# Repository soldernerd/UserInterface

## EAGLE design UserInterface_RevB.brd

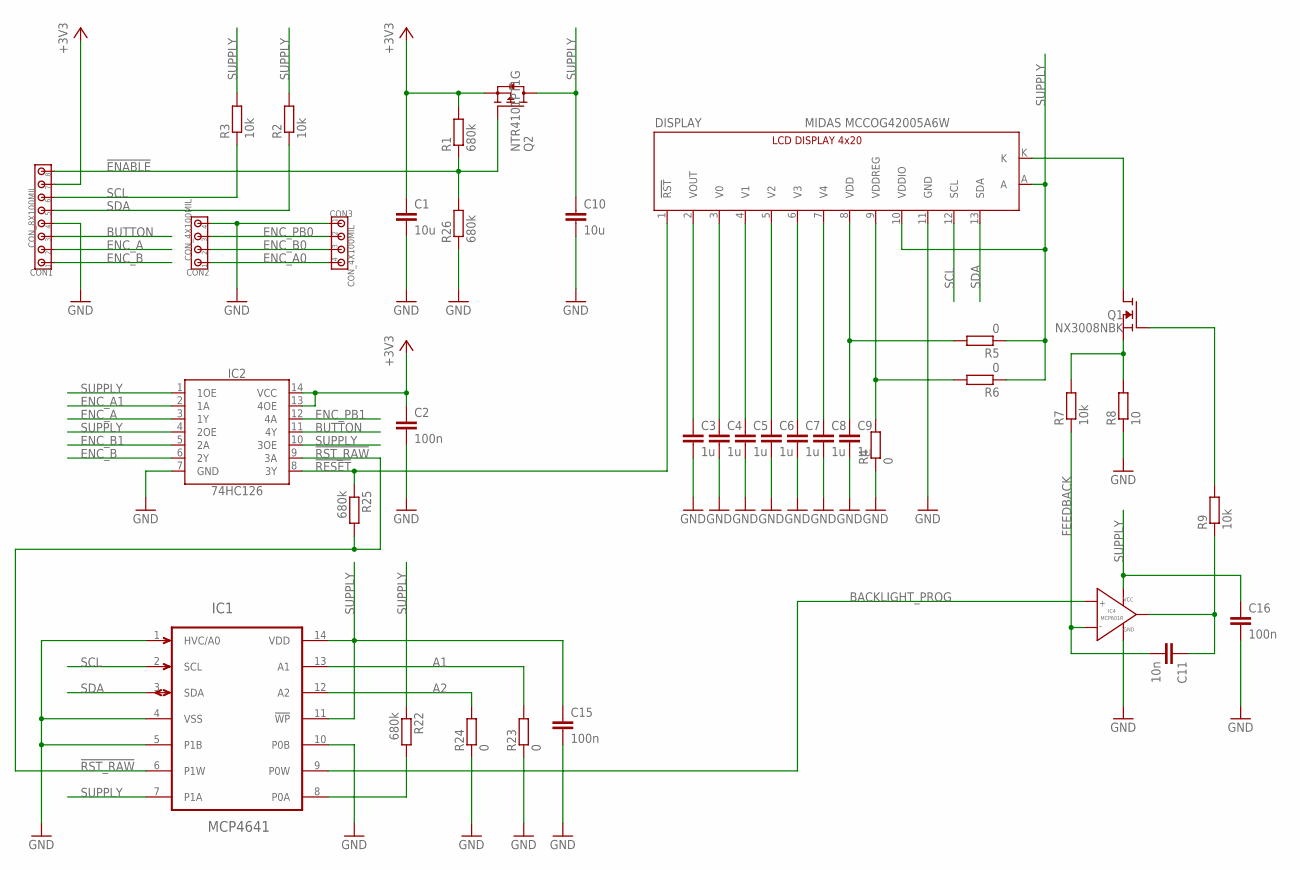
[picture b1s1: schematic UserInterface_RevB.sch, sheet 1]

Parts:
C1, C10: 10u; C0805
C2, C15, C16: 100n; C0805
C3, C4, C5, C6, C7, C8, C9: 1u; C0805
C11: 10n; C0805
CON1: CON_8X100MIL; 100MIL_8X
CON2, CON3: CON_4X100MIL; 100MIL_4X
DISPLAY: MIDAS MCCOG42005A6W; LCD_4X20_I2C
IC1: MCP4641; TSSOP14
IC2: 74HC126; SO14
IC4: MCP601R; SOT-23-5
Q1: NX3008NBK; SOT23
Q2: NTR4101PT1G; SOT23
R1, R22, R25, R26: 680k; R0805
R2, R3, R7, R9: 10k; R0805
R4, R5, R6, R23, R24: 0; R0805
R8: 10; R0805

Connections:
!ENABLE!: CON1.8, Q2.1 (G), R1.1, R26.2
!RESET!: DISPLAY.1 (!RST!), IC2.8 (3Y), R25.1
!RST_RAW!: IC1.6 (P1W), IC2.9 (3A), R25.2
+3V3: C1.1, C2.1, CON1.7, IC2.13 (4OE), IC2.14 (VCC), Q2.2 (S), R1.2; also elsewhere on the board
A1: IC1.13 (A1), R23.2
A2: IC1.12 (A2), R24.2
BACKLIGHT_PROG: IC1.9 (P0W), IC4.3 (VIN+)
BUTTON: CON1.3, IC2.11 (4Y); also elsewhere on the board
ENC_A: CON1.2, IC2.3 (1Y); also elsewhere on the board
ENC_A0: CON2.1, CON3.4; also elsewhere on the board
ENC_A1: IC2.2 (1A); also elsewhere on the board
ENC_B: CON1.1, IC2.6 (2Y); also elsewhere on the board
ENC_B0: CON2.2, CON3.3; also elsewhere on the board
ENC_B1: IC2.5 (2A); also elsewhere on the board
ENC_PB0: CON2.3, CON3.2; also elsewhere on the board
ENC_PB1: IC2.12 (4A); also elsewhere on the board
FEEDBACK: C11.2, IC4.4 (VIN-), R7.1
GND: C1.2, C2.2, C3.2, C4.2, C5.2, C6.2, C7.2, C8.2, C9.2, C10.2, C15.2, C16.2, CON1.4, CON2.4, CON3.1, DISPLAY.11 (GND), IC1.1 (HVC/A0), IC1.4 (VSS), IC1.5 (P1B), IC1.10 (P0B), IC2.7 (GND), IC4.5 (GND), R4.1, R8.1, R23.1, R24.1, R26.1; also elsewhere on the board
LED_K: DISPLAY.K, Q1.3 (D)
unnamed: C3.1, DISPLAY.2 (VOUT)
unnamed: C4.1, DISPLAY.3 (V0)
unnamed: C8.1, DISPLAY.7 (V4)
unnamed: C7.1, DISPLAY.6 (V3)
unnamed: C6.1, DISPLAY.5 (V2)
unnamed: C5.1, DISPLAY.4 (V1)
unnamed: C11.1, IC4.1 (VOUT), R9.1
unnamed: Q1.1 (G), R9.2
unnamed: Q1.2 (S), R7.2, R8.2
unnamed: IC1.8 (P0A), R22.2
SCL: CON1.6, DISPLAY.12 (SCL), IC1.2 (SCL), R3.1
SDA: CON1.5, DISPLAY.13 (SDA), IC1.3 (SDA), R2.1
SUPPLY: C10.1, C15.1, C16.1, DISPLAY.10 (VDDIO), DISPLAY.A, IC1.7 (P1A), IC1.11 (!WP!), IC1.14 (VDD), IC2.1 (1OE), IC2.4 (2OE), IC2.10 (3OE), IC4.2 (VCC), Q2.3 (D), R2.2, R3.2, R5.1, R6.1, R22.1; also elsewhere on the board
VDD: C9.1, DISPLAY.8 (VDD), R5.2
VDREG: DISPLAY.9 (VDDREG), R4.2, R6.2

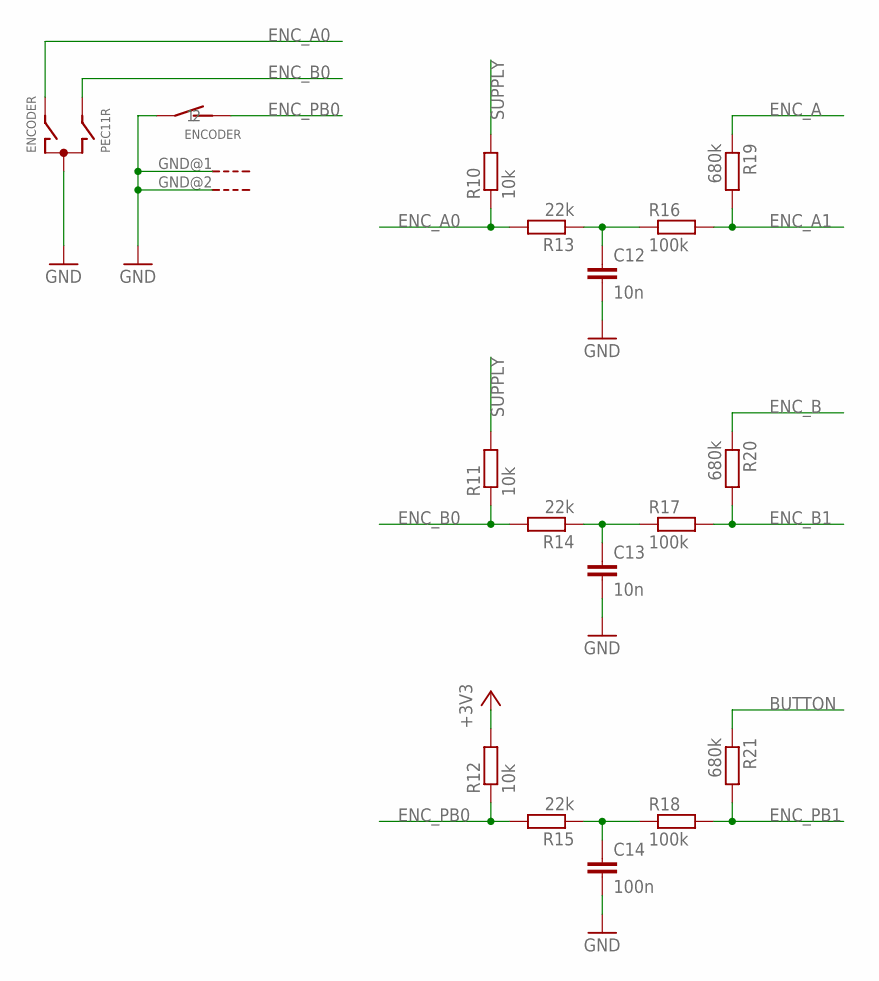
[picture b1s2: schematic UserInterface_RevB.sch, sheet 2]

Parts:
C12, C13: 10n; C0805
C14: 100n; C0805
ENCODER: PEC11R; ENCODER_BOURNS
R10, R11, R12: 10k; R0805
R13, R14, R15: 22k; R0805
R16, R17, R18: 100k; R0805
R19, R20, R21: 680k; R0805

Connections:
+3V3: R12.2; also elsewhere on the board
BUTTON: R21.1; also elsewhere on the board
ENC_A: R19.1; also elsewhere on the board
ENC_A0: ENCODER.A, R10.1, R13.2; also elsewhere on the board
ENC_A1: R16.2, R19.2; also elsewhere on the board
ENC_B: R20.1; also elsewhere on the board
ENC_B0: ENCODER.B, R11.1, R14.2; also elsewhere on the board
ENC_B1: R17.2, R20.2; also elsewhere on the board
ENC_PB0: ENCODER.1, R12.1, R15.2; also elsewhere on the board
ENC_PB1: R18.2, R21.2; also elsewhere on the board
GND: C12.2, C13.2, C14.2, ENCODER.2, ENCODER.C, ENCODER.GND@1 (G), ENCODER.GND@2 (G); also elsewhere on the board
unnamed: C13.1, R14.1, R17.1
unnamed: C12.1, R13.1, R16.1
unnamed: C14.1, R15.1, R18.1
SUPPLY: R10.2, R11.2; also elsewhere on the board

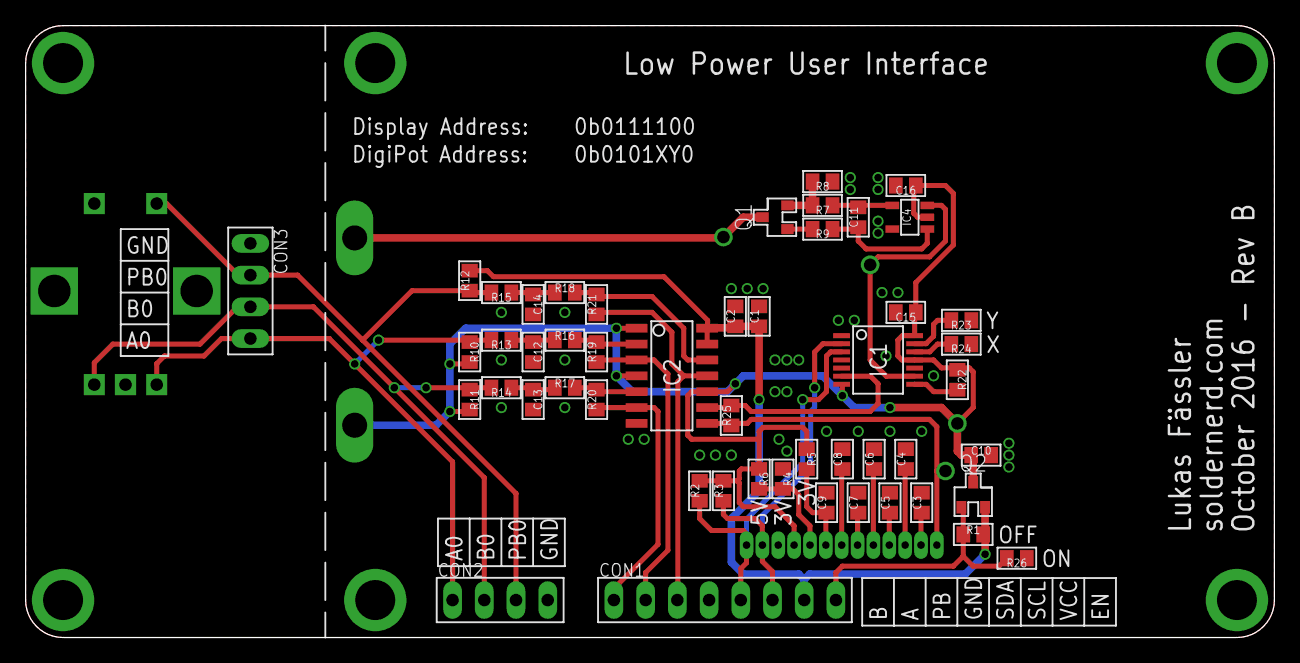
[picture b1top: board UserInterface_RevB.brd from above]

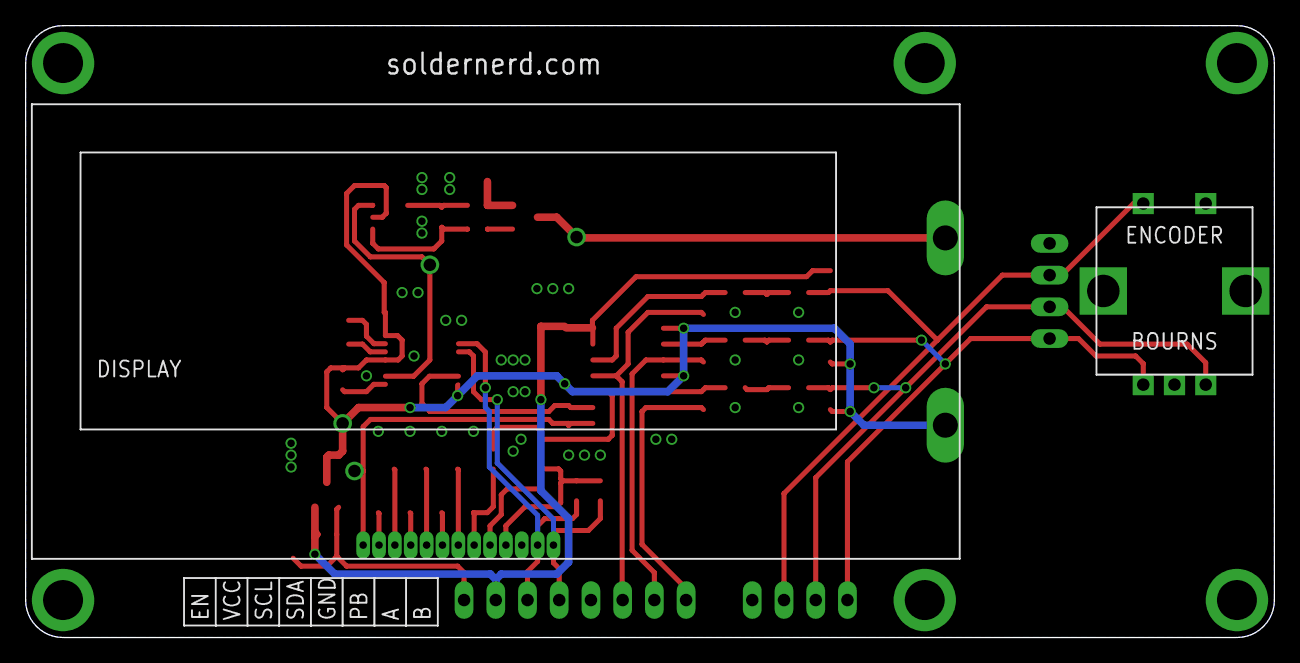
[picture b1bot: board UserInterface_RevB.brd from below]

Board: 2 copper layers, 100.0 x 49.0 mm, 52 parts (2 on the bottom side), 37 nets.

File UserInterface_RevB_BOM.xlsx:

Qty | Value | Device | Package | Parts | Description
5 | 0R | RESISTORR0805 | R0805 | R4, R5, R6, R23, R24 | RESISTOR, European symbol
1 | 10R | RESISTORR0805 | R0805 | R8 | RESISTOR, European symbol
3 | 100k | RESISTORR0805 | R0805 | R16, R17, R18 | RESISTOR, European symbol
4 | 100n | CC0805 | C0805 | C2, C14, C15, C16 | Capacitor
7 | 10k | RESISTORR0805 | R0805 | R2, R3, R7, R9, R10, R11, R12 | RESISTOR, European symbol
3 | 10n | CC0805 | C0805 | C11, C12, C13 | Capacitor
2 | 10u | CC0805 | C0805 | C1, C10 | Capacitor
7 | 1u | CC0805 | C0805 | C3, C4, C5, C6, C7, C8, C9 | Capacitor
3 | 22k | RESISTORR0805 | R0805 | R13, R14, R15 | RESISTOR, European symbol
7 | 680k | RESISTORR0805 | R0805 | R1, R19, R20, R21, R22, R25, R26 | RESISTOR, European symbol
1 | 74HC126 | 74HC126 | SO14 | IC2 | Quad buffer/line driver; 3-state
1 | MCP4641 | MCP4641 | TSSOP14 | IC1 | Dual DigiPot with 128 steps and non-volatile memory
1 | MCP601R | MCP601R | SOT-23-5 | IC4 | Rail-to-Rail OpAmp (Marking SM07)
1 | MIDAS MCCOG42005A6W | LCD4X20_I2C | LCD_4X20_I2C | DISPLAY | 4x20 character LCD display with I2C interface
1 | NTR4101PT1G | P-FETSOT23 | SOT23 | Q2 | P-Channel MOSFET (Marking TR4)
1 | NX3008NBK | N-FETSOT23 | SOT23 | Q1 | N-Channel MOSFET (Marking KS)
1 | PEC11R | ENCODER_BOURNS | ENCODER_BOURNS | ENCODER | Bourns Rotary Encoder with Switch
